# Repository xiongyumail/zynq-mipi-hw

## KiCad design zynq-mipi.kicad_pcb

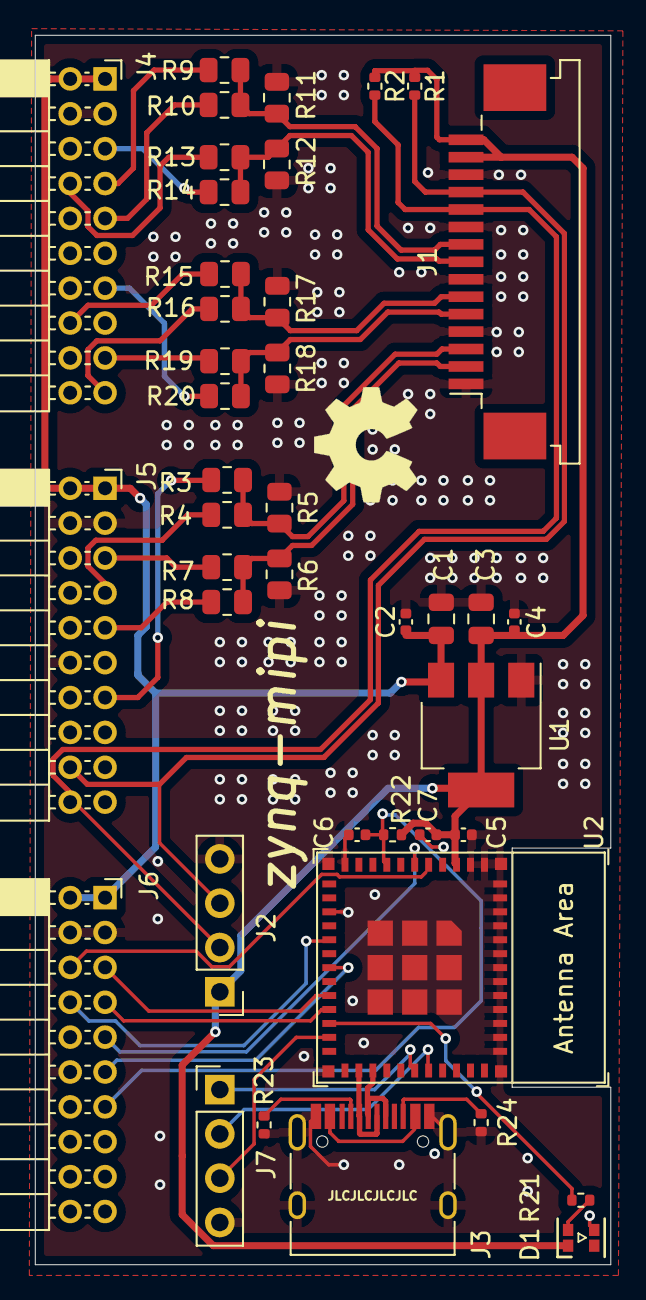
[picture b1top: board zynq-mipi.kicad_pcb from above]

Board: 2 copper layers, 33.0 x 70.5 mm, 41 parts (0 on the bottom side), 40 nets.

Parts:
C1, C3: 10uF; C_0805_2012Metric
C2, C4, C7: 0.1uF; C_0402_1005Metric
C5, C6: 1uF; C_0402_1005Metric
D1: WS2812B-0807
J1: DSI; TE_1-84953-5_1x15-1MP_P1.0mm_Horizontal
J2: I2C; PinHeader_1x04_P2.54mm_Vertical
J3: HRO_TYPE-C-31-M-12
J4: ZYNQ_DATA1; PinSocket_2x10_P2.00mm_Horizontal
J5: ZYNQ_DATA2; PinSocket_2x10_P2.00mm_Horizontal
J6: ZYNQ_DATA3; PinSocket_2x10_P2.00mm_Horizontal
J7: DBG; PinHeader_1x04_P2.54mm_Vertical
R1, R2: 4.7k; R_0402_1005Metric
R3, R8, R9, R14, R15, R20: 68R1; R_0805_2012Metric
R4, R7, R10, R13, R16, R19: 619; R_0805_2012Metric
R5, R6, R11, R12, R17, R18: 51; R_0805_2012Metric
R21: 0; R_0402_1005Metric
R22: 10K; R_0402_1005Metric
R23: 5K1; R_0402_1005Metric
R24: 5K1R; R_0402_1005Metric
U1: NCP1117-3.3_SOT223; SOT-223-3_TabPin2
U2: ESP32-C3-MINI-1

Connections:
+3V3: C3.1, C4.1, C5.1, C7.1, D1.1 (VDD), J1.14, J1.15, J2.1, R1.1, R2.1, R22.1, U1.2 (VO), U2.3 (3V3)
+5V: C1.1, C2.1, J4.1, J4.2, J5.1, J5.2, J6.1, J6.2, U1.3 (VI)
/CLK_HS_N: J4.17, R19.2
/CLK_HS_P: J4.19, R16.2
/CLK_LP_N: J4.13, R20.2
/CLK_LP_P: J4.16, R15.1
/CLK_N: J1.5, R18.2, R19.1, R20.1
/CLK_P: J1.6, R15.2, R16.1, R17.1
/CS: J6.8, U2.16 (GPIO10)
/D0_HS_N: J4.8, R13.2
/D0_HS_P: J4.9, R10.2
/D0_LP_N: J4.5, R14.2
/D0_LP_P: J4.7, R9.1
/D0_N: J1.8, R12.2, R13.1, R14.1
/D0_P: J1.9, R9.2, R10.1, R11.1
/D1_HS_N: J5.5, R7.2
/D1_HS_P: J5.7, R4.2
/D1_LP_N: J5.9, R8.2
/D1_LP_P: J5.13, R3.1
/D1_N: J1.2, R6.2, R7.1, R8.1
/D1_P: J1.3, R3.2, R4.1, R5.1
/DATAREADY: J6.11, U2.18 (GPIO4/ADC1_CH4)
/HANDSHAKE: J6.9, U2.6 (GPIO3/ADC1_CH3)
/I2C_SCL: J1.11, J2.2, J5.20, R2.2
/I2C_SDA: J1.12, J2.3, J5.18, R1.2
/MISO: J6.6, U2.5 (GPIO2/ADC1_CH2)
/MOSI: J6.7, U2.21 (GPIO7)
/RST: C6.2, J6.13, R22.2, U2.8 (EN/CHIP_PU)
/SCLK: J6.5, U2.20 (GPIO6)
/esp_hosted/BOOT: J7.3, U2.23 (GPIO9)
/esp_hosted/RXD: J7.1, U2.30 (GPIO20/U0RXD)
/esp_hosted/TXD: J7.2, U2.31 (GPIO21/U0TXD)
/esp_hosted/USB_D+: J3.A6 (D+), J3.B6 (D+), U2.27 (GPIO19/USB_D+)
/esp_hosted/USB_D-: J3.A7 (D-), J3.B7 (D-), U2.26 (GPIO18/USB_D-)
GNDD: C1.2, C2.2, C3.2, C4.2, C5.2, C6.1, C7.2, D1.3 (VSS), J1.1, J1.4, J1.7, J1.10, J1.13, J2.4, J3.A1 (GND), J3.A12 (GND), J3.B1 (GND), J3.B12 (GND), J3.S1 (SHIELD), J4.3, J4.4, J4.12, J5.3, J5.4, J5.12, J6.3, J6.4, J6.12, J7.4, R5.2, R6.1, R11.2, R12.1, R17.2, R18.1, R23.2, R24.2, U1.1 (GND), U2.1 (GND), U2.2 (GND), U2.11 (GND), U2.14 (GND), U2.36 (GND)
unnamed: D1.4 (DIN), R21.1
unnamed: J3.A5 (CC1), R23.1
unnamed: J3.B5 (CC2), R24.1
unnamed: R21.2, U2.22 (GPIO8)
VBUS: J3.A4 (VBUS), J3.A9 (VBUS), J3.B4 (VBUS), J3.B9 (VBUS)

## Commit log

2022-06-28 zynq-mipi
